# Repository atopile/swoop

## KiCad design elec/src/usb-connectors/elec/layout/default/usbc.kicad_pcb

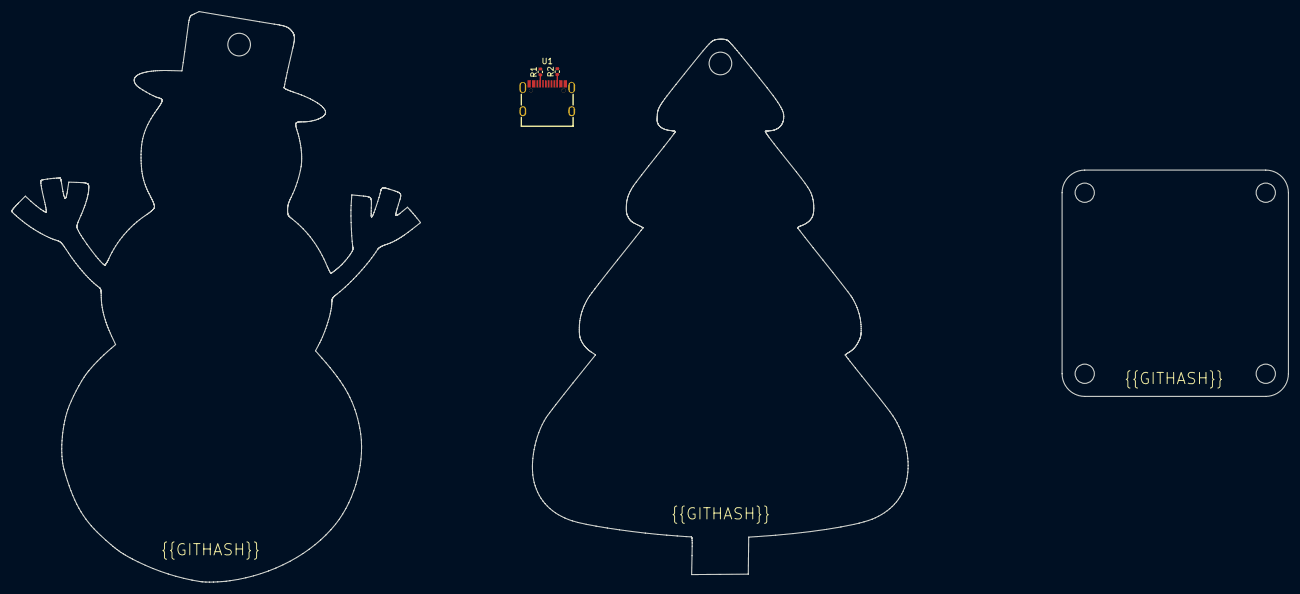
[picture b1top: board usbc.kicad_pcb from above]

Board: 2 copper layers, 66.4 x 94.6 mm, 3 parts (0 on the bottom side), 6 nets.

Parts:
R1, R2: Chip Resistor - Surface Mount 4.7KOhms ±5% 1/16W 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; R0402
U1: USB-C-SMD_KH-TYPE-C-16P

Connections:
cc1: R1.1, U1.A5
cc2: R2.1, U1.B5
dm: U1.A7, U1.B7
dp: U1.A6, U1.B6
gnd: R1.2, R2.2, U1.1, U1.2, U1.3, U1.4, U1.A1, U1.A12, U1.B1, U1.B12
vcc: U1.A4, U1.A9, U1.B4, U1.B9
